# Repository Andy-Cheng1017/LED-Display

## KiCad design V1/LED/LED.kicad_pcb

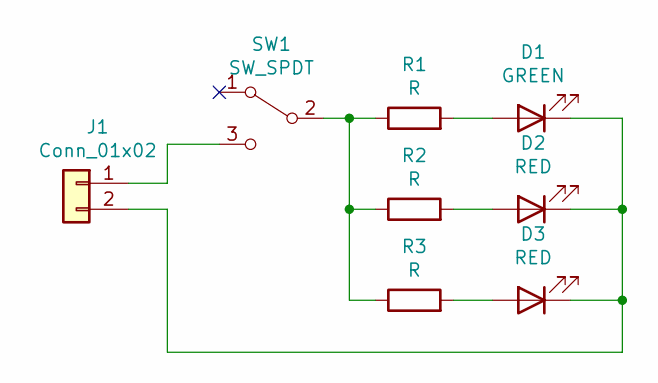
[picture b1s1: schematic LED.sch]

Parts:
D1: GREEN; LED_D5.0mm
D2, D3: RED; LED_D5.0mm
J1: Conn_01x02; JST_XH_B2B-XH-AM_1x02_P2.50mm_Vertical
R1, R2, R3: R; R_0805_2012Metric
SW1: SW_SPDT; SW_Slide_1P2T_CK_OS102011MS2Q

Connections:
unnamed: D1.1 (K), D2.1 (K), D3.1 (K), J1.2
unnamed: D1.2 (A), R1.2
unnamed: D2.2 (A), R2.2
unnamed: D3.2 (A), R3.2
unnamed: J1.1, SW1.3 (C)
unnamed: R1.1, R2.1, R3.1, SW1.2 (B)

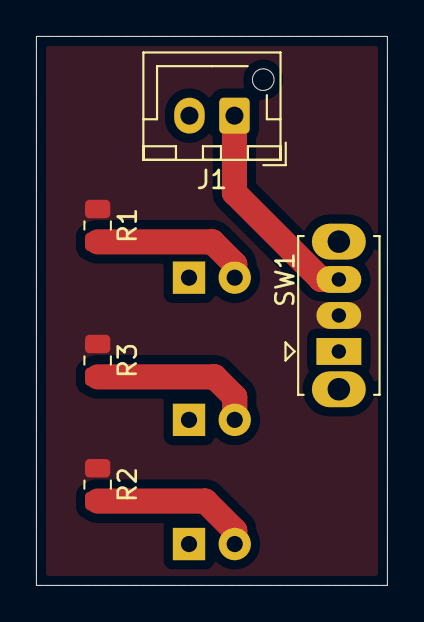
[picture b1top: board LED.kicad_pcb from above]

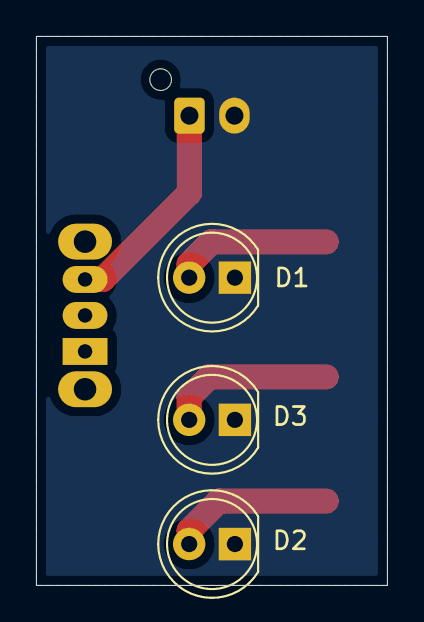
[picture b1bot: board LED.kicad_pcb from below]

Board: 2 copper layers, 19.5 x 30.5 mm, 8 parts (3 on the bottom side), 6 nets.
